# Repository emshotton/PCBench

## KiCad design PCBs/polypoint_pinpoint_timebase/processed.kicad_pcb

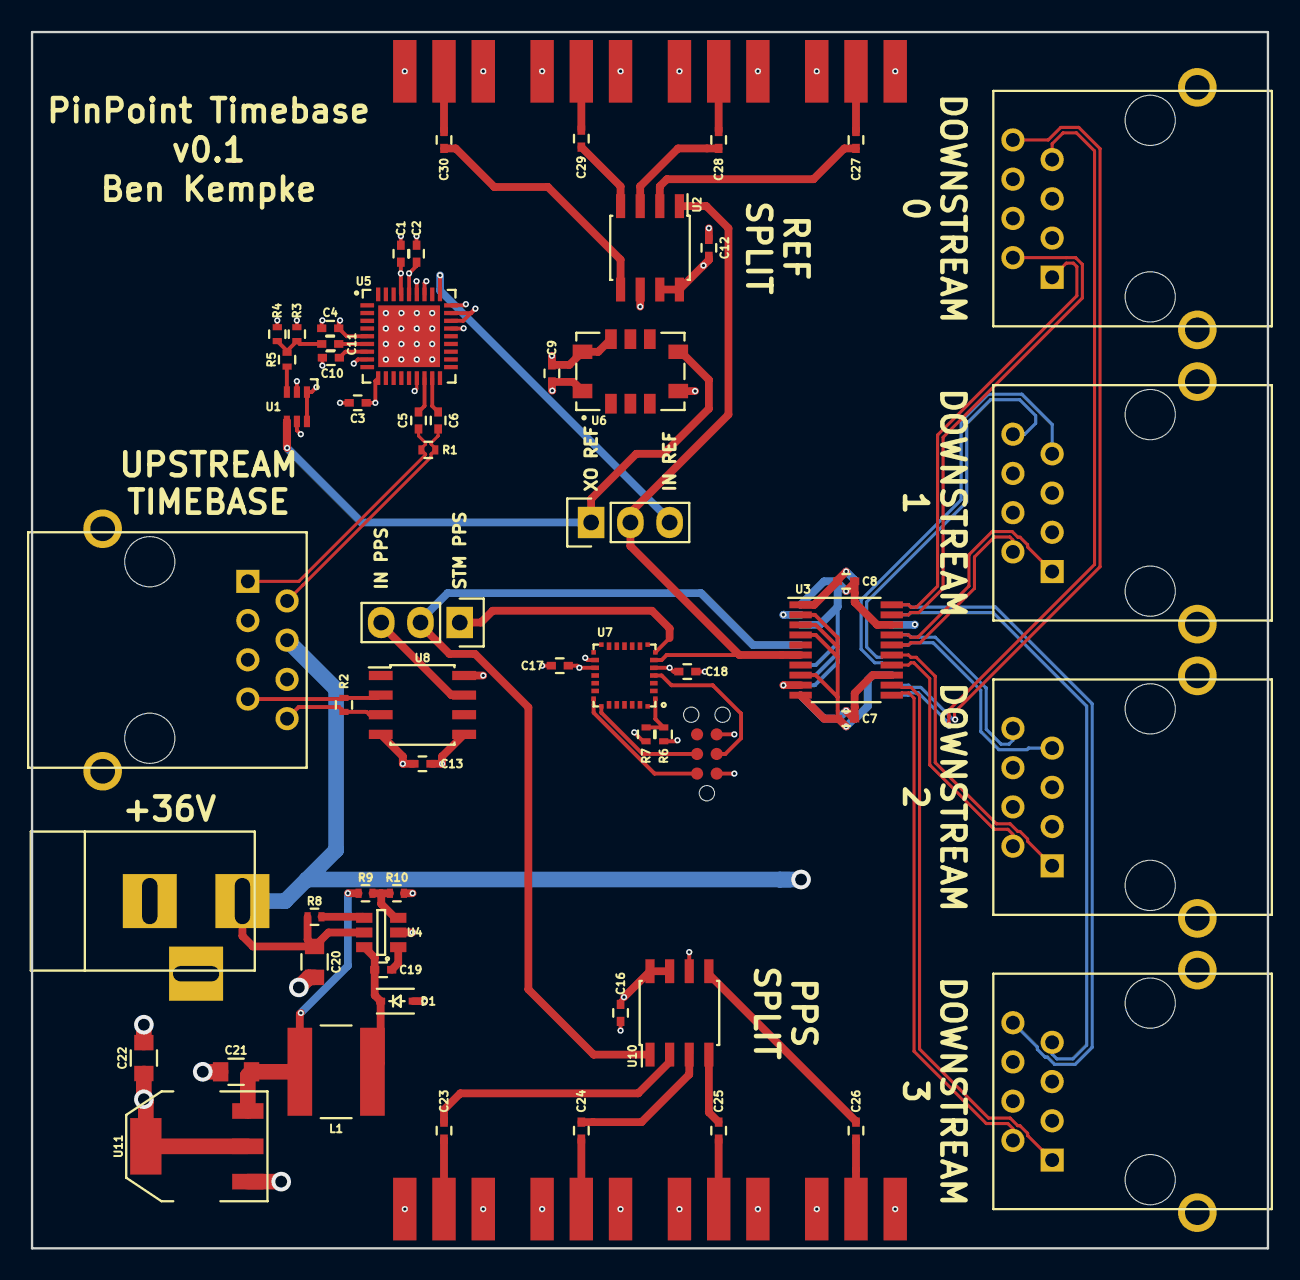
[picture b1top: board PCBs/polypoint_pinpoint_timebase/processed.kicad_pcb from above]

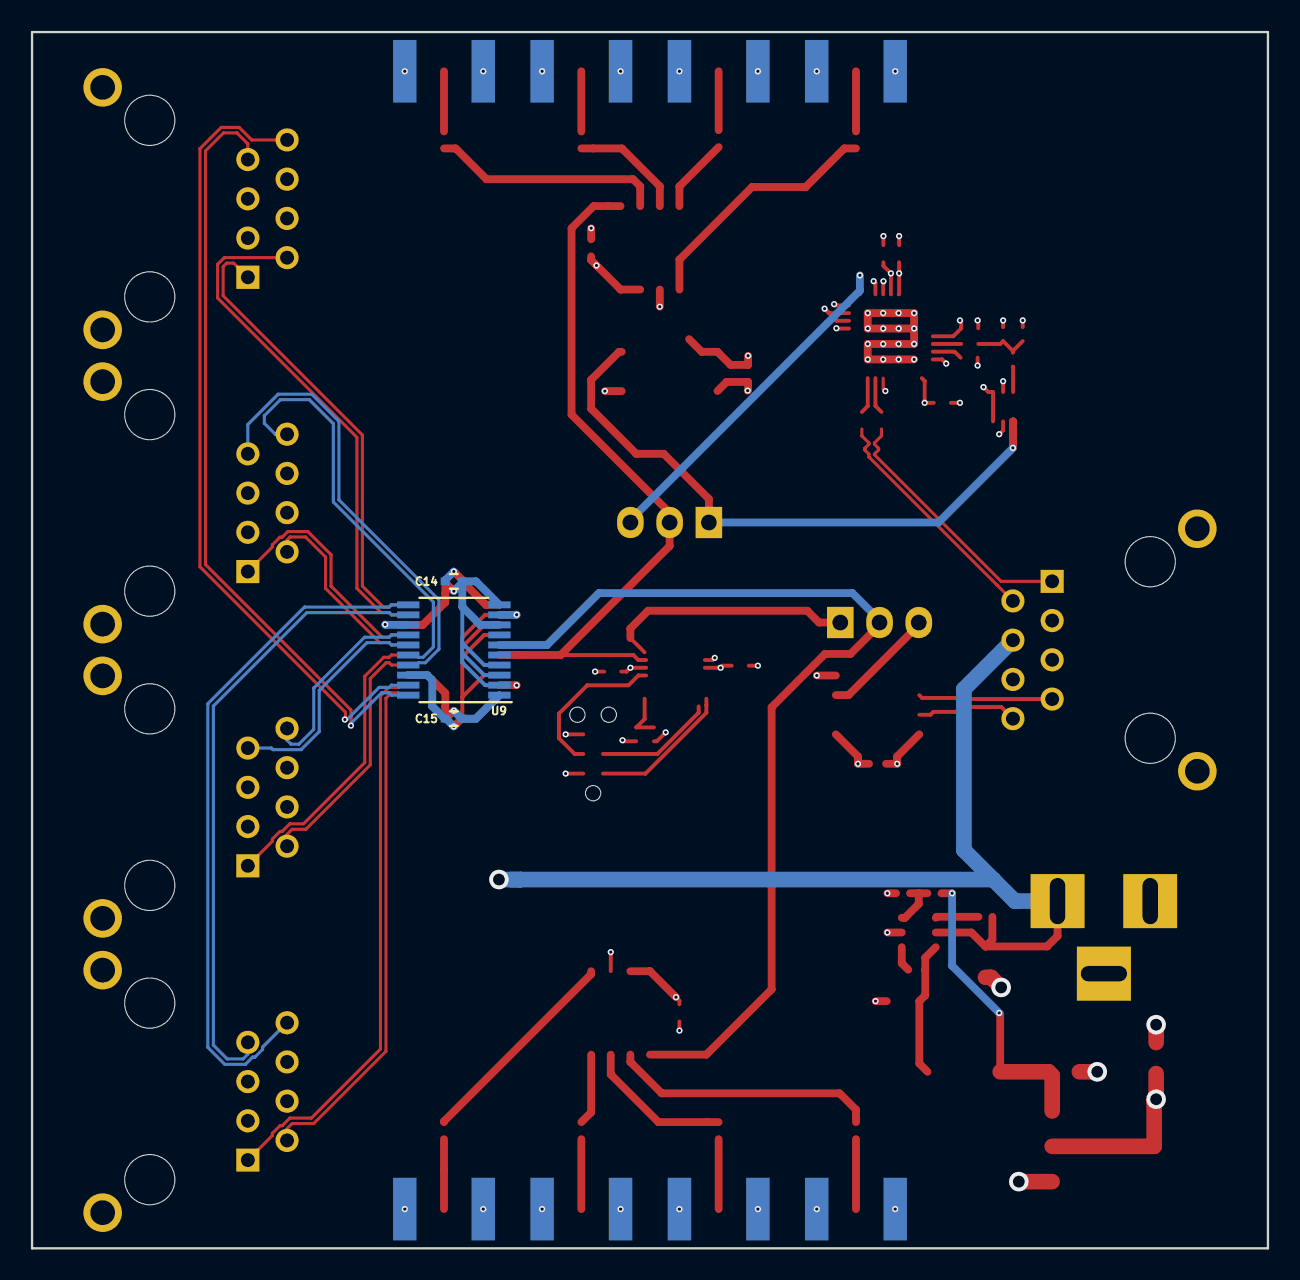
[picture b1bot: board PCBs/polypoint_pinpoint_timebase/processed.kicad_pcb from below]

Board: 4 copper layers, 80.0 x 78.7 mm, 70 parts (3 on the bottom side), 60 nets.

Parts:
C1, C2, C3, C4, C5, C6, C7, C8, C9, C10, C11, C12, C13, C14, C15, C16, C17, C18, C19, C23, C24, C25, C26, C27, C28, C29, C30: 0.1uF; C_0402
C20: 4.7uF; C_0805
C21, C22: 10uF; C_0805
CON1: BARREL_JACK
D1: D_Schottky; SOD-323
J1, J2, J3, J4, J5: RJ45; RJ45_8
J6: TC2030-JLINK-NL; TC2030
L1: 22uH; NR6045
P1, P6: CONN_01X03; Pin_Header_Straight_1x03
P2, P3, P4, P5, P8, P9, P10: SMA; SMA_EDGE
R1, R2, R6, R7: R_Small; R_0402
R3, R4: 150; R_0402
R5: 130; R_0402
R8: 4.7K; R_0402
R9: 49.9K; R_0402
R10: 9.53K; R_0402
U1: SN74AVC1T45; SC-70-6
U2, U10: 551S; SOIC-8_3.9x4.9mm_Pitch1.27mm
U3, U9: ICS8545; TSSOP-20_4.4x6.5mm_Pitch0.65mm
U4: AOZ1282CI; SOT-23-6
U5: SI5317; QFN-36_1EP_6x6mm
U6: 7N-XX.XXXMBP-T; 7N-xx.xxxMBP-T
U7: STM32F031G4U6; UFQFPN-28
U8: 830S21; SOIC-8_3.9x4.9mm_Pitch1.27mm
U11: NCP1117; SOT-223
eP7: SMA; SMA_EDGE

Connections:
/CLK0+: J3.1, U3.20
/CLK0-: J3.2, U3.19
/CLK1+: J4.1, U3.17
/CLK1-: J4.2, U3.16
/CLK2+: J1.1, U3.15
/CLK2-: J1.2, U3.14
/CLK3+: J5.1, U3.12
/CLK3-: J5.2, U3.11
/IN_PPS+: J2.7, R2.1, U8.2
/IN_PPS-: J2.8, R2.2, U8.3
/IN_REF+: C5.2, J2.1, R1.1
/IN_REF-: C6.2, J2.2, R1.2
/PPS0+: J3.7, U9.20
/PPS0-: J3.8, U9.19
/PPS1+: J4.7, U9.17
/PPS1-: J4.8, U9.16
/PPS2+: J1.7, U9.15
/PPS2-: J1.8, U9.14
/PPS3+: J5.7, U9.12
/PPS3-: J5.8, U9.11
/REFTMP+: C5.1, U5.16
/REFTMP-: C6.1, U5.17
/SYS_CLK: P1.2, U2.1, U3.6, U7.6
GND: C1.2, C2.1, C3.2, C4.1, C7.2, C8.1, C9.2, C10.1, C12.2, C13.2, C14.2, C15.1, C16.2, C17.2, C18.1, C20.2, C21.2, C22.2, CON1.2, CON1.3, D1.2, J1.5, J1.9, J2.5, J2.9, J3.5, J3.9, J4.5, J4.9, J5.5, J5.9, J6.5, P2.2, P3.2, P4.2, P5.2, P8.2, P9.2, P10.2, R4.1, R7.2, R10.2, U1.2, U1.5, U2.6, U3.1, U3.9, U3.13, U4.2, U5.8, U5.15, U5.24, U5.27, U5.30, U5.31, U5.37, U6.4, U6.10, U7.16, U8.5, U9.1, U9.9, U9.13, U10.6, U11.1, eP7.2
unnamed: C10.2, U5.7
unnamed: C11.1, R3.1, R4.2, R5.2
unnamed: C11.2, U5.6
unnamed: C19.1, D1.1, L1.1, U4.6
unnamed: C19.2, U4.1
unnamed: C21.1, L1.2, R9.1, U11.3
unnamed: C23.1, U10.2
unnamed: C23.2, eP7.1
unnamed: C24.1, U10.3
unnamed: C24.2, P8.1
unnamed: C25.1, U10.4
unnamed: C25.2, P9.1
unnamed: C26.1, U10.5
unnamed: C26.2, P10.1
unnamed: C27.1, U2.2
unnamed: C27.2, P2.1
unnamed: C28.1, U2.3
unnamed: C28.2, P3.1
unnamed: C29.1, U2.4
unnamed: C29.2, P4.1
unnamed: C30.1, U2.5
unnamed: C30.2, P5.1
unnamed: J6.2, U7.21
unnamed: J6.3, U7.4
unnamed: J6.4, U7.22
unnamed: P1.1, U1.4, U6.5
unnamed: P1.3, U5.28
unnamed: P6.1, U7.7
unnamed: P6.2, U9.6, U10.1
unnamed: P6.3, U8.7
unnamed: R5.1, U1.3
unnamed: R6.1, R7.1, U7.1
unnamed: R8.2, U4.4
unnamed: R9.2, R10.1, U4.3
V3P3: C1.1, C2.2, C3.1, C4.2, C7.1, C8.2, C9.1, C12.1, C13.1, C14.1, C15.2, C16.1, C17.1, C18.2, C22.1, J6.1, R3.2, R6.2, U1.1, U1.6, U2.7, U2.8, U3.2, U3.3, U3.4, U3.8, U3.10, U3.18, U5.5, U5.10, U5.25, U5.26, U5.32, U5.33, U6.8, U6.9, U7.5, U7.17, U8.4, U8.8, U9.2, U9.3, U9.4, U9.8, U9.10, U9.18, U10.7, U10.8, U11.2, U11.4
VDD: C20.1, CON1.1, J1.4, J2.4, J3.4, J4.4, J5.4, R8.1, U4.5

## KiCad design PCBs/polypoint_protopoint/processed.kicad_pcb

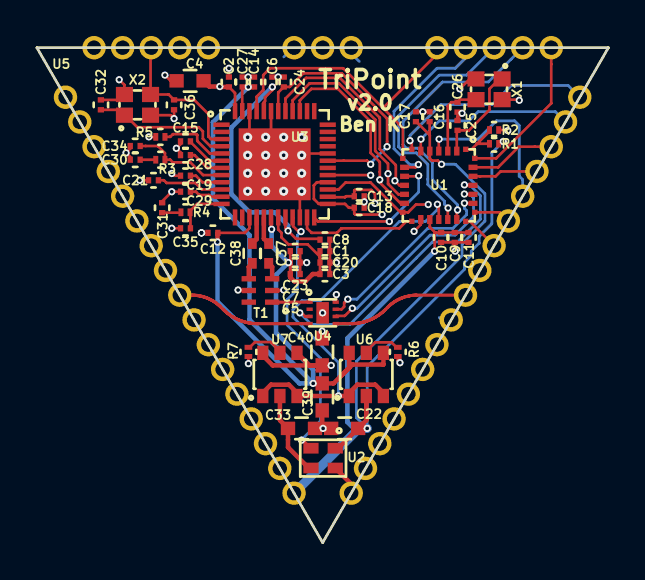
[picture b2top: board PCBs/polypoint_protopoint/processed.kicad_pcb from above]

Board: 4 copper layers, 31.8 x 27.5 mm, 57 parts (0 on the bottom side), 56 nets.

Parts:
C1, C3, C11: 10pF; C_0201
C2, C6, C9, C13, C14, C15, C16, C18, C19, C20, C21, C23, C24, C27, C28, C29: 0.1uF; C_0201
C4, C22: 4.7uF; C_0603
C5, C7: 330pF; C_0201
C8, C10, C17: 100pF; C_0201
C12: 0.01uF; C_0201
C25, C26, C32, C36: 12pF; C_0201
C30: 27pF; C_0201
C31: 820pF; C_0201
C33, C39, C40: 10uF; C_0603
C34: 1.2pF; C_0201
C35: 18pF; C_0201
C37, C38: 12pF; C_0402
R1, R2, R5: 11k; R_0201
R3: 16k; R_0201
R4: 270; R_0201
R6, R7: 100; R_0201
T1: HHM1595A1
U1: STM32F031G6U6; UFQFPN-28
U2: LXDC2HL
U3: DW1000; QFN-48-EP-6x6mm
U4: SKY13317; MLPQ-UT-8-1.5X1.5mm
U5: ProtoPoint_Module; ProtoPoint_Module_Castellated
U6, U7: AO6604; TSOP-6
X1: 38.4M; FA-128
X2: 16M; FA-128

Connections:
/ANT_SEL0: U1.25, U4.3
/ANT_SEL1: U1.24, U4.6
/ANT_SEL2: U1.23, U4.7
/DW_IRQ: U1.8, U3.45, U5.39
/DW_PWR_SW: U1.18, U6.1, U6.3, U7.1, U7.3
/DW_SYNC: U3.29, U5.19
/DW_WAKEUP: U1.15, U3.23
/DW_XTAL1: C36.1, U3.3, U5.49, X2.3
/GPIO0: U1.26, U5.31
/GPIO1: U1.27, U5.32
/GPIO2: U1.6, U5.33
/GPIO3: U1.7, U5.34
/GPIO4: U1.28, U5.35
/I2C_SCL: U1.19, U5.37
/I2C_SDA: U1.20, U5.36
/INTERRUPT: U1.9, U5.38
/MCU_NRST: U1.4, U5.30
/MCU_SWCLK: U1.22, U5.29
/MCU_SWDIO: U1.21, U5.28
/RF0: U4.4, U5.9
/RF1: U4.5, U5.26
/RF2: U4.8, U5.43
/SPI1_CLK: U1.11, U3.41, U5.22
/SPI1_MISO: U1.12, U3.40, U5.21
/SPI1_MOSI: U1.13, U3.39, U5.20
/V1P8_En: U2.2, U3.21
/~DW_RST: U1.14, U3.27, U5.24
/~SPI1_SS: U1.10, U3.24, U5.23
GND: C1.2, C2.2, C3.2, C4.2, C5.2, C6.2, C7.2, C8.2, C9.2, C10.2, C11.2, C12.2, C13.2, C14.2, C15.2, C16.1, C17.1, C18.2, C19.2, C20.2, C21.2, C22.2, C23.2, C24.2, C25.2, C26.2, C27.2, C28.2, C29.2, C30.2, C31.2, C32.2, C33.2, C34.2, C35.2, C36.2, C39.2, C40.2, R2.1, R5.2, R6.1, R7.1, T1.2, T1.5, U1.16, U2.4, U3.22, U3.32, U3.43, U3.46, U3.49, U4.9, U5.8, U5.10, U5.18, U5.25, U5.27, U5.42, U5.44, X1.2, X1.4, X2.2, X2.4
unnamed: C25.1, U1.2, X1.1
unnamed: C26.1, U1.3, X1.3
unnamed: C30.1, R3.2
unnamed: C31.1, R4.2
unnamed: C32.1, U3.4, X2.1
unnamed: C34.1, R3.1, U3.8
unnamed: C35.1, R4.1, U3.12
unnamed: C37.1, T1.3
unnamed: C37.2, U3.17
unnamed: C38.1, T1.4
unnamed: C38.2, U3.16
unnamed: R1.2, R2.2, U1.1
unnamed: R5.1, U3.5
unnamed: R6.2, U6.5
unnamed: R7.2, U7.5
unnamed: T1.1, U4.1
V1P8: C33.1, U2.3, U7.2
V1P8_SW: C2.1, C4.1, C13.1, C40.1, U3.26, U3.48, U7.4, U7.6
V3P3: C9.1, C10.1, C11.1, C16.2, C17.2, C22.1, R1.1, U1.5, U1.17, U2.1, U5.17, U6.2
V3P3_SW: C1.1, C3.1, C5.1, C7.1, C12.1, C14.1, C18.1, C20.1, C23.1, C27.1, C39.1, U3.15, U3.18, U3.19, U3.25, U3.28, U3.47, U6.4, U6.6
VDDCLK: C19.1, U3.9
VDDDIG: C6.1, C8.1, U3.20, U3.44
VDDIF: C28.1, U3.7
VDDIO: C24.1, U3.31, U3.42
VDDMS: C15.1, U3.6
VDDSYN: C21.1, U3.10
VDDVCO: C29.1, U3.11

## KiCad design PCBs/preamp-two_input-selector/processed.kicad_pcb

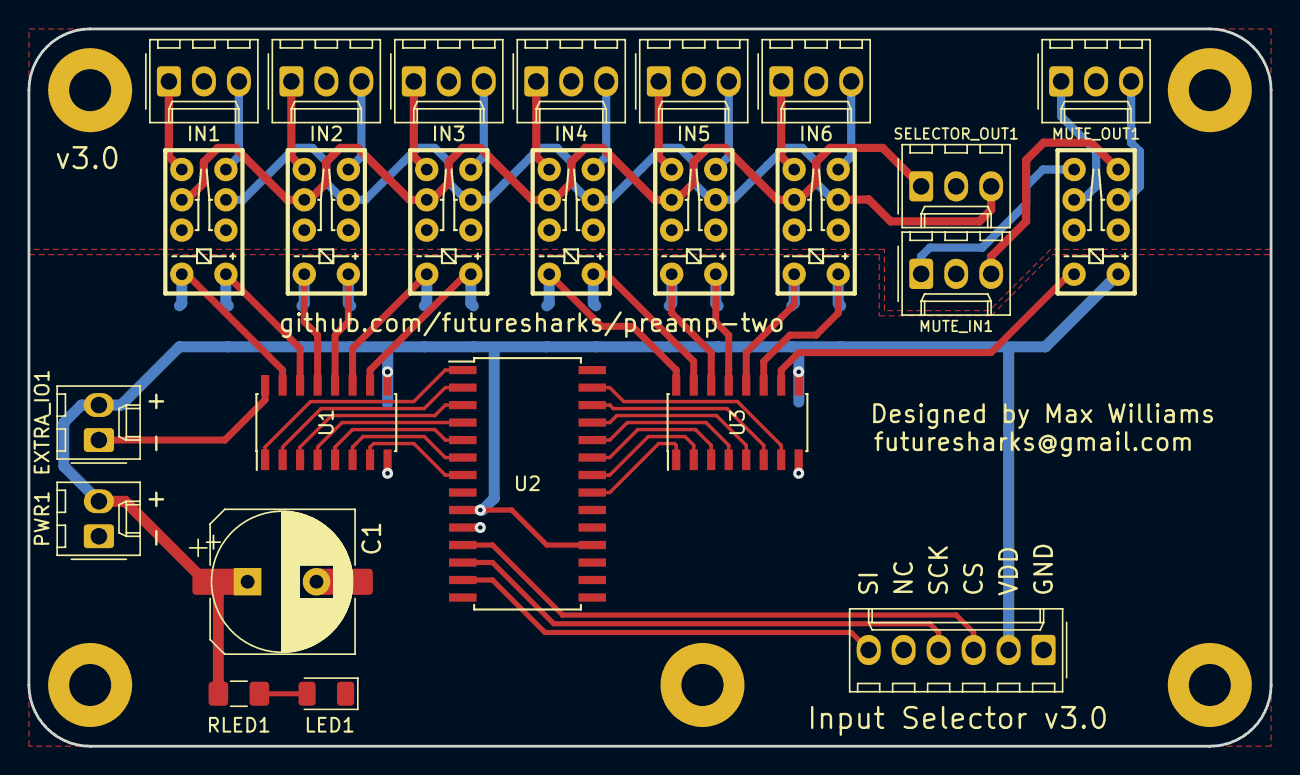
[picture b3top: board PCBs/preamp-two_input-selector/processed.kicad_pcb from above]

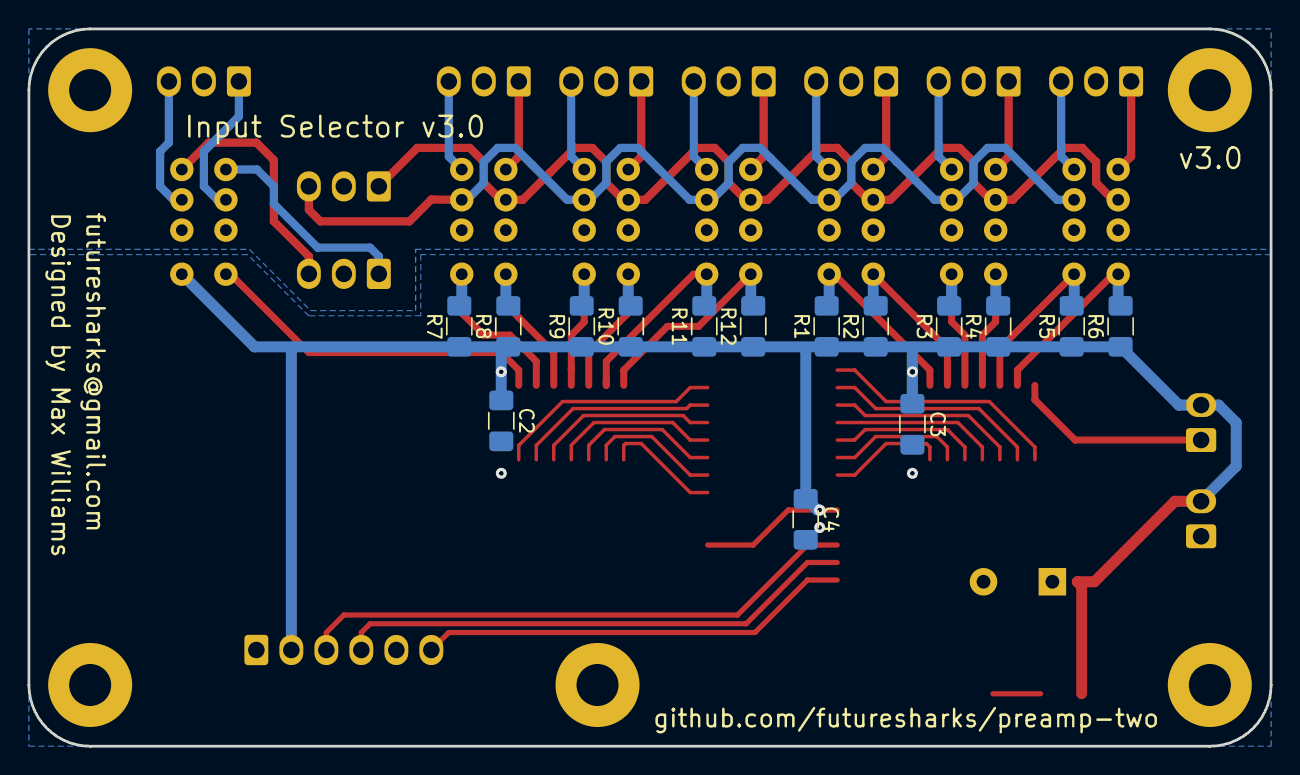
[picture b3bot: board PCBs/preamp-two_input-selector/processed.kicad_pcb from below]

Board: 2 copper layers, 90.2 x 52.1 mm, 46 parts (15 on the bottom side), 53 nets.

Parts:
C1_SMD1: CP; CP_Elec_10x7.9
C1_TH1: CP; CP_Radial_D10.0mm_P5.00mm
C2, C3, C4: C; C_1206_3216Metric_Pad1.42x1.75mm_HandSolder
EXTRA_IO1: Conn_01x02_Male; Molex_KK-254_AE-6410-02A_1x02_P2.54mm_Vertical
H1, H2, H3, H4, H5: MountingHole; MountingHole_3.2mm_M3_DIN965
IN1, IN2, IN3, IN4, IN5, IN6: Conn_01x03_Male; Molex_KK-254_AE-6410-03A_1x03_P2.54mm_Vertical
J1: Conn_01x06_Male; Molex_KK-254_AE-6410-06A_1x06_P2.54mm_Vertical
K1, K2, K3, K4, K5, K6: IM40; g6j-2p-y
LED1: LED; LED_1206_3216Metric
MUTE1: IM01; g6j-2p-y
MUTE_IN1: Conn_01x03_Male; Molex_KK-254_AE-6410-03A_1x03_P2.54mm_Vertical
MUTE_OUT1: Conn_01x03_Male; Molex_KK-254_AE-6410-03A_1x03_P2.54mm_Vertical
PWR1: Conn_01x02_Male; Molex_KK-254_AE-6410-02A_1x02_P2.54mm_Vertical
R1, R2, R3, R4, R5, R6, R7, R8, R9, R10, R11, R12: 47R; R_1206_3216Metric_Pad1.42x1.75mm_HandSolder
RLED1: R; R_1206_3216Metric_Pad1.42x1.75mm_HandSolder
SELECTOR_OUT1: Conn_01x03_Male; Molex_KK-254_AE-6410-03A_1x03_P2.54mm_Vertical
U1, U3: ULN2003; SOIC-16_3.9x9.9mm_P1.27mm
U2: MCP23S17_SO; SOIC-28W_7.5x17.9mm_P1.27mm

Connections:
/CS: J1.3, U2.11
/MOSI: J1.6, U2.13
/SCK: J1.4, U2.12
GND: C1_SMD1.2, C1_TH1.2, C2.2, C3.2, C4.2, J1.1, LED1.1, PWR1.1, U1.8, U2.10, U2.15, U2.16, U2.17, U3.8
GNDA: IN1.2, IN2.2, IN3.2, IN4.2, IN5.2, IN6.2, MUTE1.2, MUTE1.7, MUTE_IN1.2, MUTE_OUT1.2, SELECTOR_OUT1.2
unnamed: EXTRA_IO1.1, U1.16
unnamed: IN1.1, K1.5
unnamed: IN1.3, K1.4
unnamed: IN2.1, K2.5
unnamed: IN2.3, K2.4
unnamed: IN3.1, K3.5
unnamed: IN3.3, K3.4
unnamed: IN4.1, K4.5
unnamed: IN4.3, K4.4
unnamed: IN5.1, K5.5
unnamed: IN5.3, K5.4
unnamed: IN6.1, K6.5
unnamed: IN6.3, K6.4
unnamed: K1.1, R5.2, U1.14
unnamed: K1.3, K2.3, K3.3, K4.3, K5.3, K6.3, SELECTOR_OUT1.3
unnamed: K1.6, K2.6, K3.6, K4.6, K5.6, K6.6, SELECTOR_OUT1.1
unnamed: K1.8, R6.2, U1.15
unnamed: K2.1, R3.2, U1.12
unnamed: K2.8, R4.2, U1.13
unnamed: K3.1, R1.2, U1.10
unnamed: K3.8, R2.2, U1.11
unnamed: K4.1, R11.2, U3.15
unnamed: K4.8, R12.2, U3.16
unnamed: K5.1, R9.2, U3.13
unnamed: K5.8, R10.2, U3.14
unnamed: K6.1, R7.2, U3.11
unnamed: K6.8, R8.2, U3.12
unnamed: LED1.2, RLED1.2
unnamed: MUTE1.3, MUTE_OUT1.3
unnamed: MUTE1.4, MUTE_IN1.3
unnamed: MUTE1.5, MUTE_IN1.1
unnamed: MUTE1.6, MUTE_OUT1.1
unnamed: MUTE1.8, U3.10
unnamed: U1.1, U2.1
unnamed: U1.2, U2.2
unnamed: U1.3, U2.3
unnamed: U1.4, U2.4
unnamed: U1.5, U2.5
unnamed: U1.6, U2.6
unnamed: U1.7, U2.7
unnamed: U2.21, U3.1
unnamed: U2.22, U3.2
unnamed: U2.23, U3.3
unnamed: U2.24, U3.4
unnamed: U2.25, U3.5
unnamed: U2.26, U3.6
unnamed: U2.27, U3.7
VDD: C1_SMD1.1, C1_TH1.1, C2.1, C3.1, C4.1, EXTRA_IO1.2, J1.2, MUTE1.1, PWR1.2, R1.1, R2.1, R3.1, R4.1, R5.1, R6.1, R7.1, R8.1, R9.1, R10.1, R11.1, R12.1, RLED1.1, U1.9, U2.9, U2.18, U3.9

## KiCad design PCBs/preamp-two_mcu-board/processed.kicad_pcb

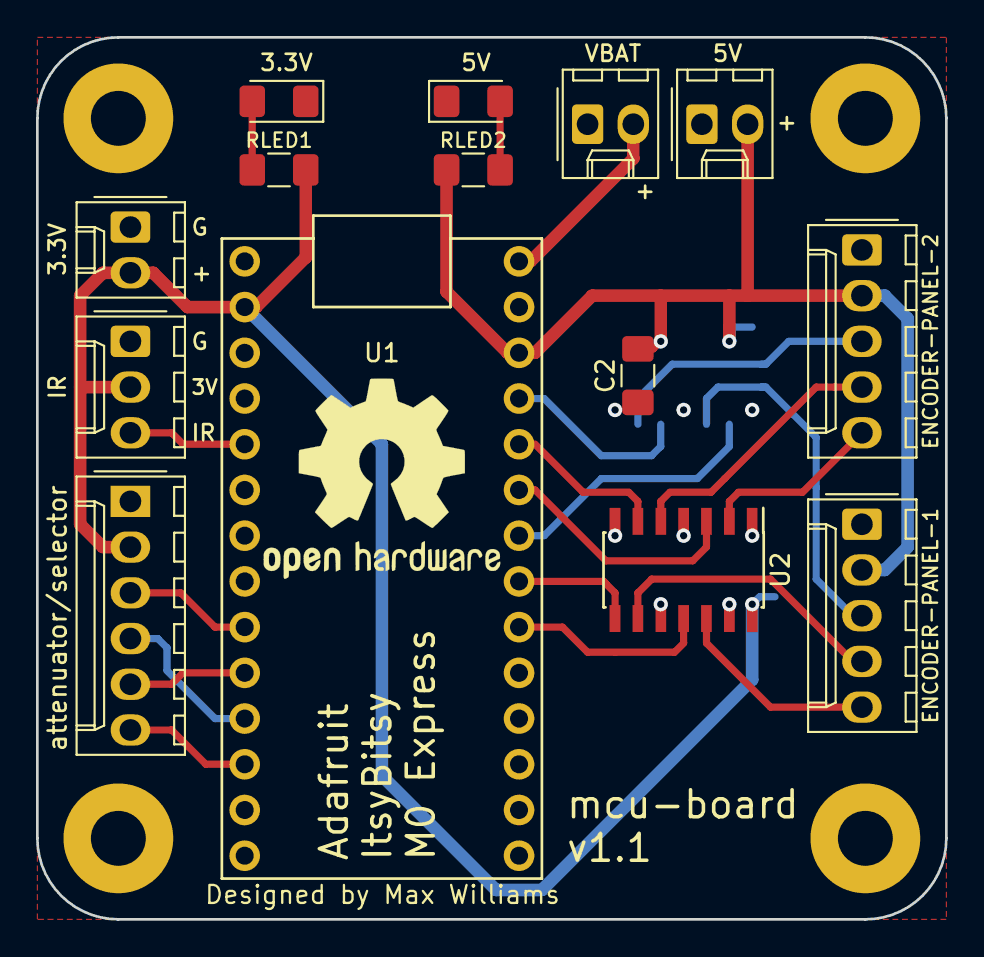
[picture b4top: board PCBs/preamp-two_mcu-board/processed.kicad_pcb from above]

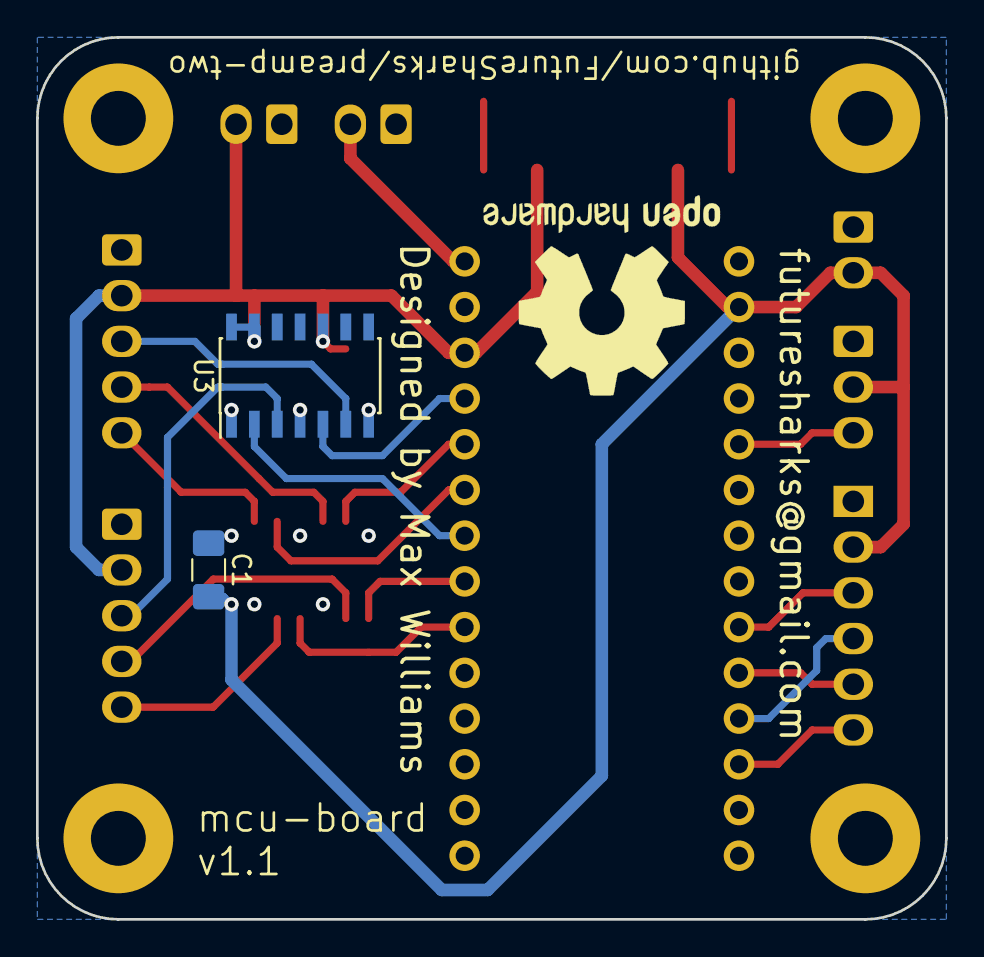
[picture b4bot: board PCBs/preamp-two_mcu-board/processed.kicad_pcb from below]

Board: 2 copper layers, 50.5 x 49.0 mm, 22 parts (3 on the bottom side), 23 nets.

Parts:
3.3V1: 3.3V; Molex_KK-254_AE-6410-02A_1x02_P2.54mm_Vertical
5V1: 5V; Molex_KK-254_AE-6410-02A_1x02_P2.54mm_Vertical
C1, C2: C; C_1206_3216Metric_Pad1.42x1.75mm_HandSolder
ENCODER-PANEL-1: ENCODER-PANEL-1; Molex_KK-254_AE-6410-05A_1x05_P2.54mm_Vertical
ENCODER-PANEL-2: ENCODER-PANEL-2; Molex_KK-254_AE-6410-05A_1x05_P2.54mm_Vertical
H1, H2, H3, H4: MountingHole_Pad; MountingHole_3.2mm_M3_Pad
IR1: Conn_01x03; Molex_KK-254_AE-6410-03A_1x03_P2.54mm_Vertical
J5: MDAC-INPUT-SELECTOR; Molex_KK-254_AE-6410-06A_1x06_P2.54mm_Vertical
LED_3V1, LED_5V1: LED; LED_1206_3216Metric_Pad1.42x1.75mm_HandSolder
LOGO1, LOGO2: Logo_Open_Hardware_Small; OSHW-Logo2_14.6x12mm_SilkScreen
RLED1, RLED2: R; R_1206_3216Metric_Pad1.42x1.75mm_HandSolder
U1: m0-express
U2, U3: SN74AHCT125DR; SOIC-14_3.9x8.7mm_P1.27mm
VBAT1: V-BAT; Molex_KK-254_AE-6410-02A_1x02_P2.54mm_Vertical

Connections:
+3V3: 3.3V1.2, C1.2, IR1.2, J5.2, RLED1.1, U1.2, U2.14
+5V: 5V1.2, C2.2, ENCODER-PANEL-1.2, ENCODER-PANEL-2.2, RLED2.1, U1.26, U3.10, U3.13, U3.14
BAT: U1.28, VBAT1.2
CS_input_selector: J5.3, U1.9
CS_mdac_attenuator: J5.5, U1.10
GND: 3.3V1.1, 5V1.1, C1.1, C2.1, ENCODER-PANEL-1.1, ENCODER-PANEL-2.1, IR1.1, J5.1, LED_3V1.1, LED_5V1.1, U1.27, U2.1, U2.4, U2.7, U2.10, U2.13, U3.1, U3.4, U3.7, VBAT1.1
IR_SENSOR: IR1.3, U1.5
MOSI: J5.6, U1.12
unnamed: LED_3V1.2, RLED1.2
unnamed: LED_5V1.2, RLED2.2
SCK: J5.4, U1.11
panel_1_encoder_A_3v: U1.20, U2.11
panel_1_encoder_A_5v: ENCODER-PANEL-1.5, U2.12
panel_1_encoder_B_3v: U1.21, U2.8
panel_1_encoder_B_5v: ENCODER-PANEL-1.4, U2.9
panel_1_neopixel_3v: U1.22, U3.2
panel_1_neopixel_5v: ENCODER-PANEL-1.3, U3.3
panel_2_encoder_A_3v: U1.23, U2.3
panel_2_encoder_A_5v: ENCODER-PANEL-2.5, U2.2
panel_2_encoder_B_3v: U1.24, U2.6
panel_2_encoder_B_5v: ENCODER-PANEL-2.4, U2.5
panel_2_neopixel_3v: U1.25, U3.5
panel_2_neopixel_5v: ENCODER-PANEL-2.3, U3.6

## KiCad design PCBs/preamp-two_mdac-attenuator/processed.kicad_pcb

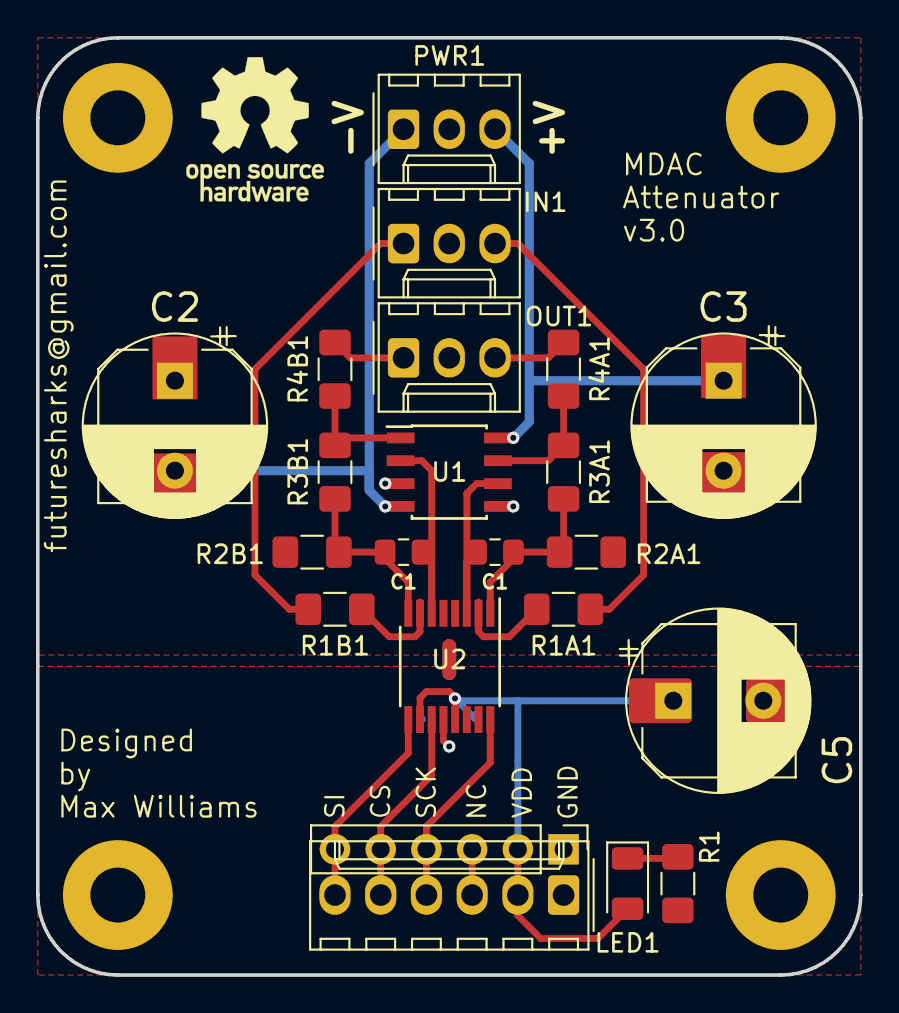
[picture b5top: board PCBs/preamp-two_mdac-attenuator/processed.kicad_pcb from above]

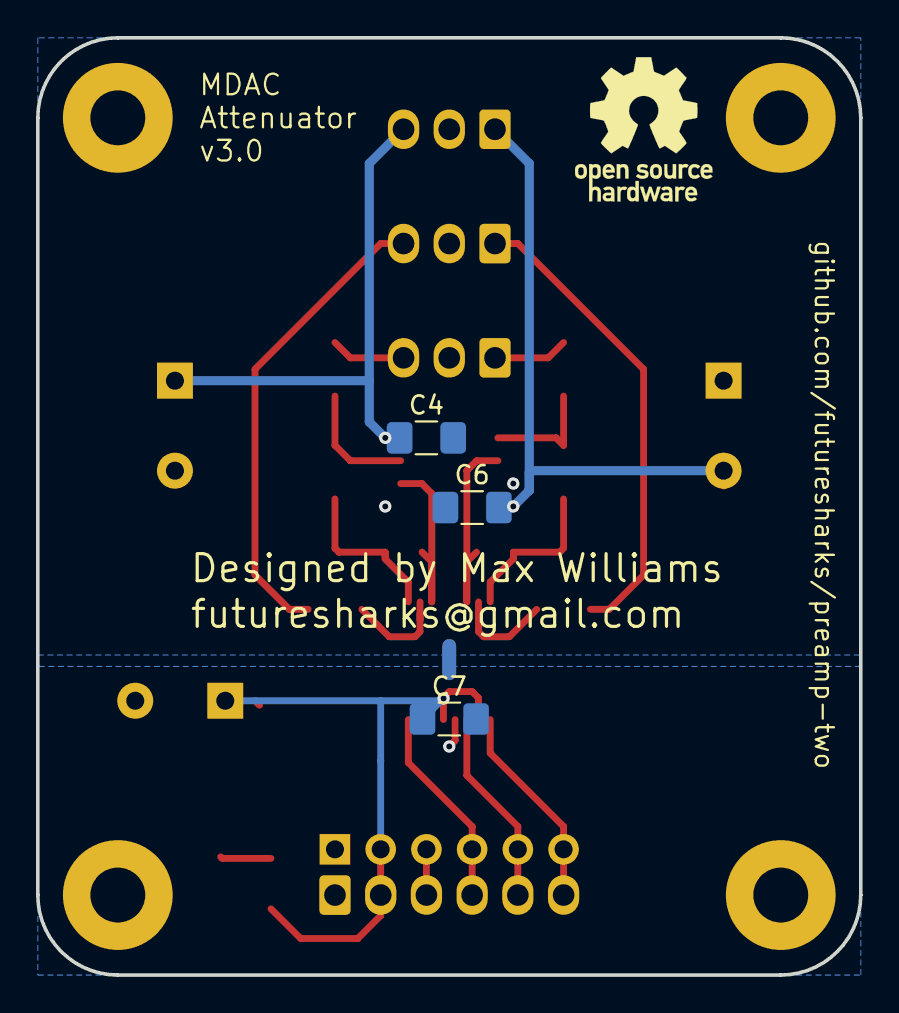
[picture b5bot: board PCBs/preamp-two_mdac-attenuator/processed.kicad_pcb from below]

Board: 2 copper layers, 45.7 x 52.1 mm, 34 parts (4 on the bottom side), 21 nets.

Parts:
C1A1, C1B1: 2pF; C_0805_2012Metric_Pad1.15x1.40mm_HandSolder
C2_SMD1, C3_SMD1, C5_SMD1: CP; CP_Elec_8x10
C2_TH1, C3_TH1, C5_TH1: CP; CP_Radial_D10.0mm_P5.00mm
C4, C6, C7: 100nF; C_1206_3216Metric_Pad1.42x1.75mm_HandSolder
H1, H2, H3, H4: MountingHole; MountingHole_3.2mm_M3_DIN965
IN1: Conn_01x03_Male; Molex_KK-254_AE-6410-03A_1x03_P2.54mm_Vertical
J1: Conn_01x06_Male; Molex_KK-254_AE-6410-06A_1x06_P2.54mm_Vertical
J2: Conn_01x06_Male; PinHeader_1x06_P2.54mm_Vertical
LED1: LED; LED_1206_3216Metric
LOGO1, LOGO2: Logo_Open_Hardware_Small; OSHW-Logo_7.5x8mm_SilkScreen
OUT1: Conn_01x03_Male; Molex_KK-254_AE-6410-03A_1x03_P2.54mm_Vertical
PWR1: Conn_01x03_Male; Molex_KK-254_AE-6410-03A_1x03_P2.54mm_Vertical
R1: R; R_1206_3216Metric_Pad1.42x1.75mm_HandSolder
R1A1, R1B1: 91R; R_1206_3216Metric_Pad1.42x1.75mm_HandSolder
R2A1, R2B1, R4A1, R4B1: 120R; R_1206_3216Metric_Pad1.42x1.75mm_HandSolder
R3A1, R3B1: 360R; R_1206_3216Metric_Pad1.42x1.75mm_HandSolder
U1: AD8599; SOIC-8_3.9x4.9mm_P1.27mm
U2: DAC8812ICPWG4; TSSOP-16_4.4x5mm_P0.65mm

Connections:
+15V: C3_SMD1.1, C3_TH1.1, C4.1, PWR1.3, U1.8
-15V: C2_SMD1.2, C2_TH1.2, C6.2, PWR1.1, U1.4
/CS: J1.5, J2.5, U2.11
/MOSI: J1.6, J2.6, U2.9
/SCK: J1.4, J2.4, U2.16
GNDA: C2_SMD1.1, C2_TH1.1, C3_SMD1.2, C3_TH1.2, C4.2, C5_SMD1.2, C5_TH1.2, C6.1, C7.2, IN1.2, J1.1, J2.1, OUT1.2, PWR1.2, R1.2, R2A1.2, R2B1.1, U1.3, U1.5, U2.4, U2.5, U2.12, U2.14, U2.15
unnamed: C1A1.1, U1.6, U2.3
unnamed: C1A1.2, R2A1.1, R3A1.2, U2.1
unnamed: C1B1.1, R2B1.2, R3B1.1, U2.8
unnamed: C1B1.2, U1.2, U2.6
unnamed: IN1.1, R1B1.1
unnamed: IN1.3, R1A1.2
unnamed: J1.3, J2.3
unnamed: LED1.1, R1.1
unnamed: OUT1.1, R4B1.1
unnamed: OUT1.3, R4A1.1
unnamed: R1A1.1, U2.2
unnamed: R1B1.2, U2.7
unnamed: R3A1.1, R4A1.2, U1.7
unnamed: R3B1.2, R4B1.2, U1.1
VDD: C5_SMD1.1, C5_TH1.1, C7.1, J1.2, J2.2, LED1.2, U2.10, U2.13

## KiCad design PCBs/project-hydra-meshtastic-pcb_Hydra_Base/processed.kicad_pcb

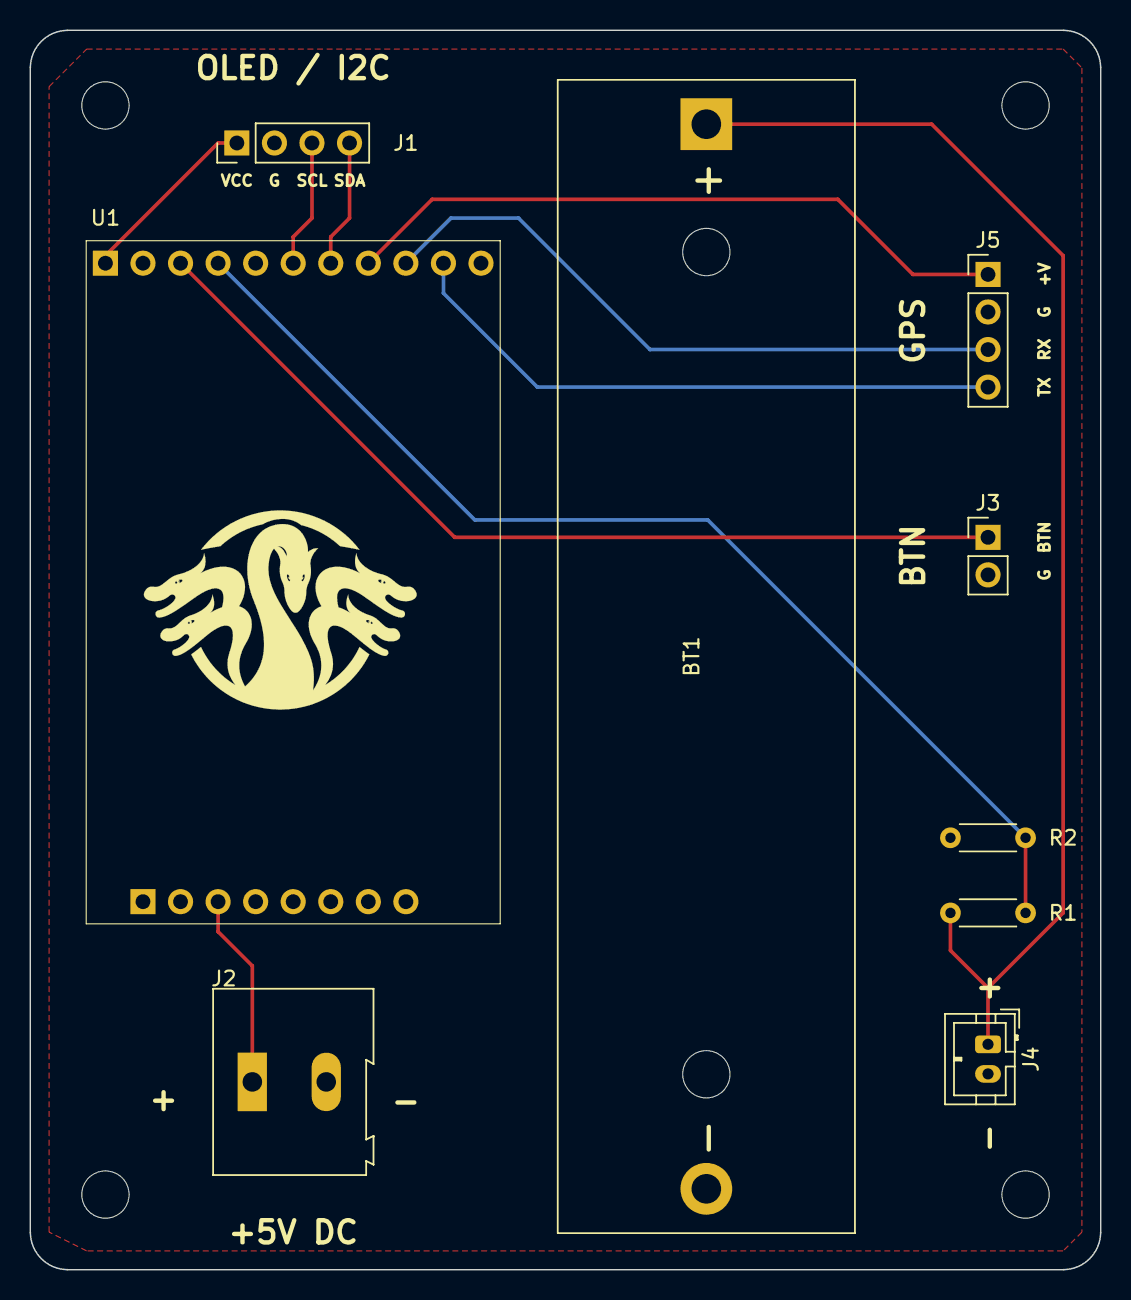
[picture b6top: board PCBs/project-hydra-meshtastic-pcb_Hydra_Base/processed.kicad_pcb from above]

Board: 2 copper layers, 72.4 x 83.8 mm, 9 parts (0 on the bottom side), 11 nets.

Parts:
BT1: Battery; BatteryHolder_MPD_BH-18650-PC2
J1, J5: Conn_01x04; PinHeader_1x04_P2.54mm_Vertical
J2: Screw_Terminal_01x02; TerminalBlock_Altech_AK300-2_P5.00mm
J3: Conn_01x02; PinHeader_1x02_P2.54mm_Vertical
J4: Conn_01x02; JST_PH_B2B-PH-K_1x02_P2.00mm_Vertical
R1, R2: R; R_Axial_DIN0204_L3.6mm_D1.6mm_P5.08mm_Horizontal
U1: Hydra_Core; Hydra_core

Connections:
+5V: J2.1, U1.14 (+5V)
GND: BT1.2 (-), J1.2, J2.2, J3.2, J4.2, J5.2, R2.2, U1.11 (GND), U1.17 (GND)
unnamed: BT1.1 (+), J4.1, R1.1
unnamed: J1.1, U1.1 (+3.3V)
unnamed: J3.1, U1.3 (USR_BTN)
unnamed: R1.2, R2.1, U1.4 (VBATT)
unnamed: J1.3, U1.6 (SCL)
unnamed: J1.4, U1.7 (SDA)
unnamed: J5.1, U1.8 (GPS_PWR)
unnamed: J5.3, U1.9 (GPS_RX)
unnamed: J5.4, U1.10 (GPS_TX)
